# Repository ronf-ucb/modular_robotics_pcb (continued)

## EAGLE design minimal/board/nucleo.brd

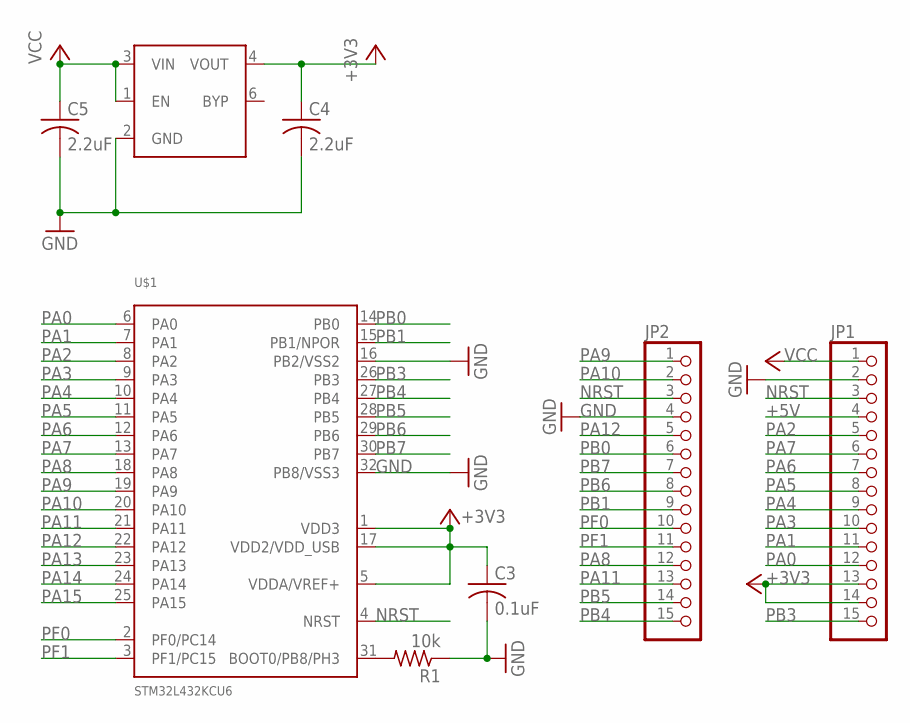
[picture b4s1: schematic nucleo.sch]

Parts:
C3: 0.1uF; C0402
C4, C5: 2.2uF; C0402
JP1, JP2: PINHD-1X15; 1X15
R1: 10k; R0402
U$1: STM32L432KCU6; QFN-32
U$3: MIC5305-MLF; MLF-6

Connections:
+3V3: C3.1, C4.1, JP1.13, JP1.14, U$1.1 (VDD3), U$1.5 (VDDA/VREF+), U$1.17 (VDD2/VDD_USB), U$3.4 (VOUT)
+5V: JP1.4
GND: C3.2, C4.2, C5.2, JP1.2, JP2.4, R1.1, U$1.16 (PB2/VSS2), U$1.32 (PB8/VSS3), U$3.2 (GND)
unnamed: R1.2, U$1.31 (BOOT0/PB8/PH3)
NRST: JP1.3, JP2.3, U$1.4 (NRST)
PA0: JP1.12, U$1.6 (PA0)
PA1: JP1.11, U$1.7 (PA1)
PA2: JP1.5, U$1.8 (PA2)
PA3: JP1.10, U$1.9 (PA3)
PA4: JP1.9, U$1.10 (PA4)
PA5: JP1.8, U$1.11 (PA5)
PA6: JP1.7, U$1.12 (PA6)
PA7: JP1.6, U$1.13 (PA7)
PA8: JP2.12, U$1.18 (PA8)
PA9: JP2.1, U$1.19 (PA9)
PA10: JP2.2, U$1.20 (PA10)
PA11: JP2.13, U$1.21 (PA11)
PA12: JP2.5, U$1.22 (PA12)
PA13: U$1.23 (PA13)
PA14: U$1.24 (PA14)
PA15: U$1.25 (PA15)
PB0: JP2.6, U$1.14 (PB0)
PB1: JP2.9, U$1.15 (PB1/NPOR)
PB3: JP1.15, U$1.26 (PB3)
PB4: JP2.15, U$1.27 (PB4)
PB5: JP2.14, U$1.28 (PB5)
PB6: JP2.8, U$1.29 (PB6)
PB7: JP2.7, U$1.30 (PB7)
PF0: JP2.10, U$1.2 (PF0/PC14)
PF1: JP2.11, U$1.3 (PF1/PC15)
VCC: C5.1, JP1.1, U$3.1 (EN), U$3.3 (VIN)

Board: 2 copper layers, 8 parts (0 on the bottom side), 27 nets, no tracks yet.

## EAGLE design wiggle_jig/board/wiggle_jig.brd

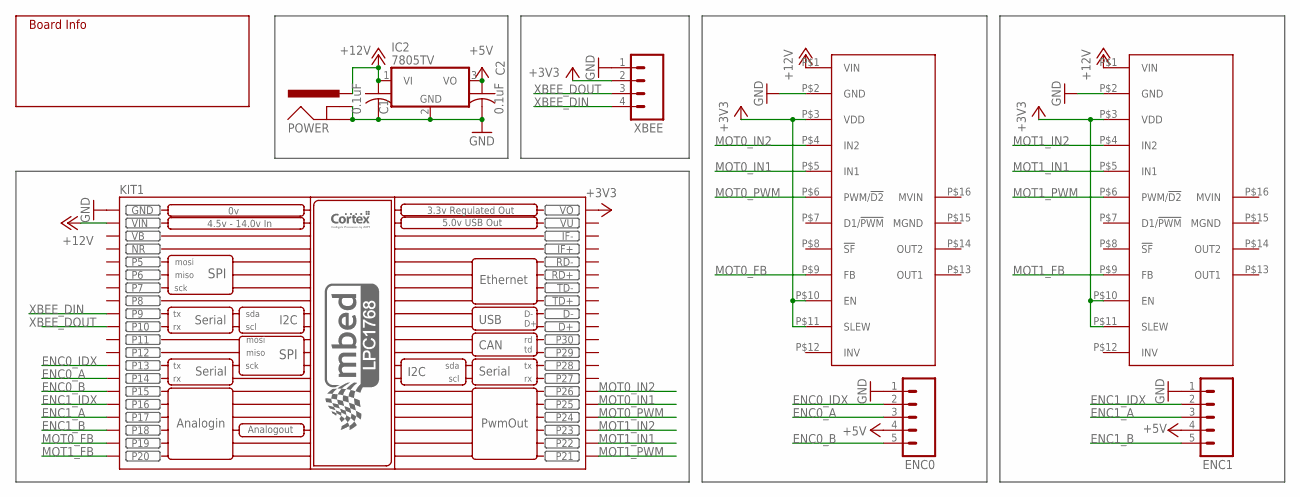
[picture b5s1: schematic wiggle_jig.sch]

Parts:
C1, C2: 0.1uF; C025-025X050
ENC0, ENC1: M05LOCK; 1X05_LOCK
IC2: 7805TV; TO220V
KIT1: MBED_NXP_LPC1768; MBED-KIT
MOT0, MOT1: MC33926_CARRIER
POWER: POWER_JACKPTH_LOCK; POWER_JACK_PTH_LOCK
U$4: INFO
XBEE: M04LOCK; 1X04_LOCK

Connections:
+3V3: KIT1.VOUT (VO), MOT0.P$3 (VDD), MOT0.P$10 (EN), MOT0.P$11 (SLEW), MOT1.P$3 (VDD), MOT1.P$10 (EN), MOT1.P$11 (SLEW), XBEE.2
+5V: C2.1, ENC0.4, ENC1.4, IC2.3 (VO)
+12V: C1.1, IC2.1 (VI), KIT1.VIN, MOT0.P$1 (VIN), MOT1.P$1 (VIN), POWER.PWR
ENC0_A: ENC0.3, KIT1.P$14 (P14)
ENC0_B: ENC0.5, KIT1.P$15 (P15)
ENC0_IDX: ENC0.2, KIT1.P$13 (P13)
ENC1_A: ENC1.3, KIT1.P$17 (P17)
ENC1_B: ENC1.5, KIT1.P$18 (P18)
ENC1_IDX: ENC1.2, KIT1.P$16 (P16)
GND: C1.2, C2.2, ENC0.1, ENC1.1, IC2.2 (GND), KIT1.GND, MOT0.P$2 (GND), MOT1.P$2 (GND), POWER.GND, POWER.GNDBREAK, XBEE.1
MOT0_FB: KIT1.P$19 (P19), MOT0.P$9 (FB)
MOT0_IN1: KIT1.P$25 (P25), MOT0.P$5 (IN1)
MOT0_IN2: KIT1.P$26 (P26), MOT0.P$4 (IN2)
MOT0_PWM: KIT1.P$24 (P24), MOT0.P$6 (PWM/!D2)
MOT1_FB: KIT1.P$20 (P20), MOT1.P$9 (FB)
MOT1_IN1: KIT1.P$22 (P22), MOT1.P$5 (IN1)
MOT1_IN2: KIT1.P$23 (P23), MOT1.P$4 (IN2)
MOT1_PWM: KIT1.P$21 (P21), MOT1.P$6 (PWM/!D2)
NR: KIT1.NR
VB: KIT1.VB
VU: KIT1.VU
XBEE_DIN: KIT1.P$9 (P9), XBEE.4
XBEE_DOUT: KIT1.P$10 (P10), XBEE.3

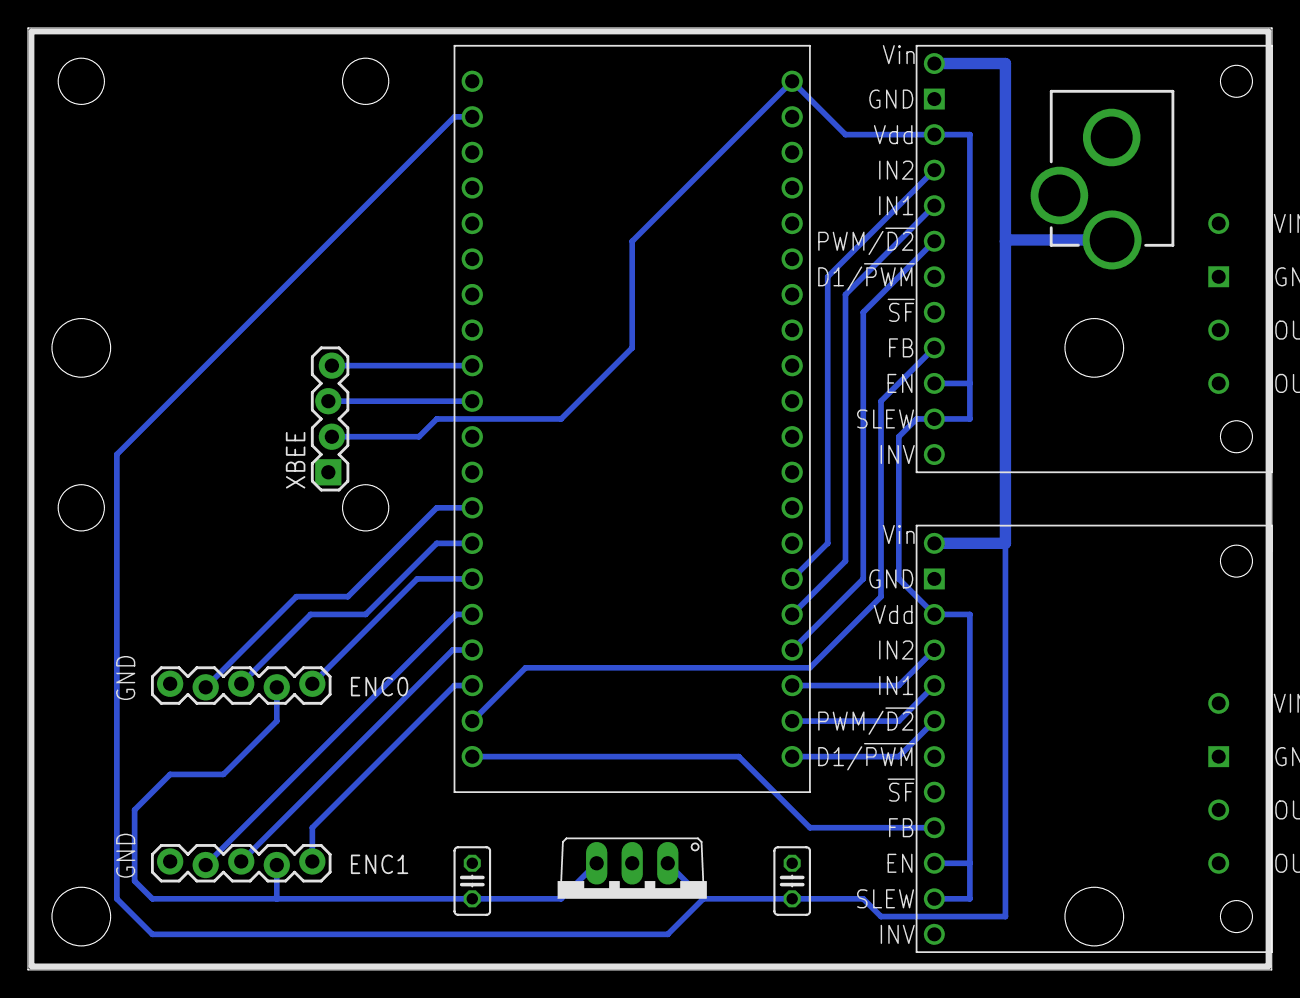
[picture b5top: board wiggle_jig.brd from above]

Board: 2 copper layers, 88.9 x 67.3 mm, 15 parts (0 on the bottom side), 20 nets.

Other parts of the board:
U$1, U$2, U$3, U$9: STAND-OFF

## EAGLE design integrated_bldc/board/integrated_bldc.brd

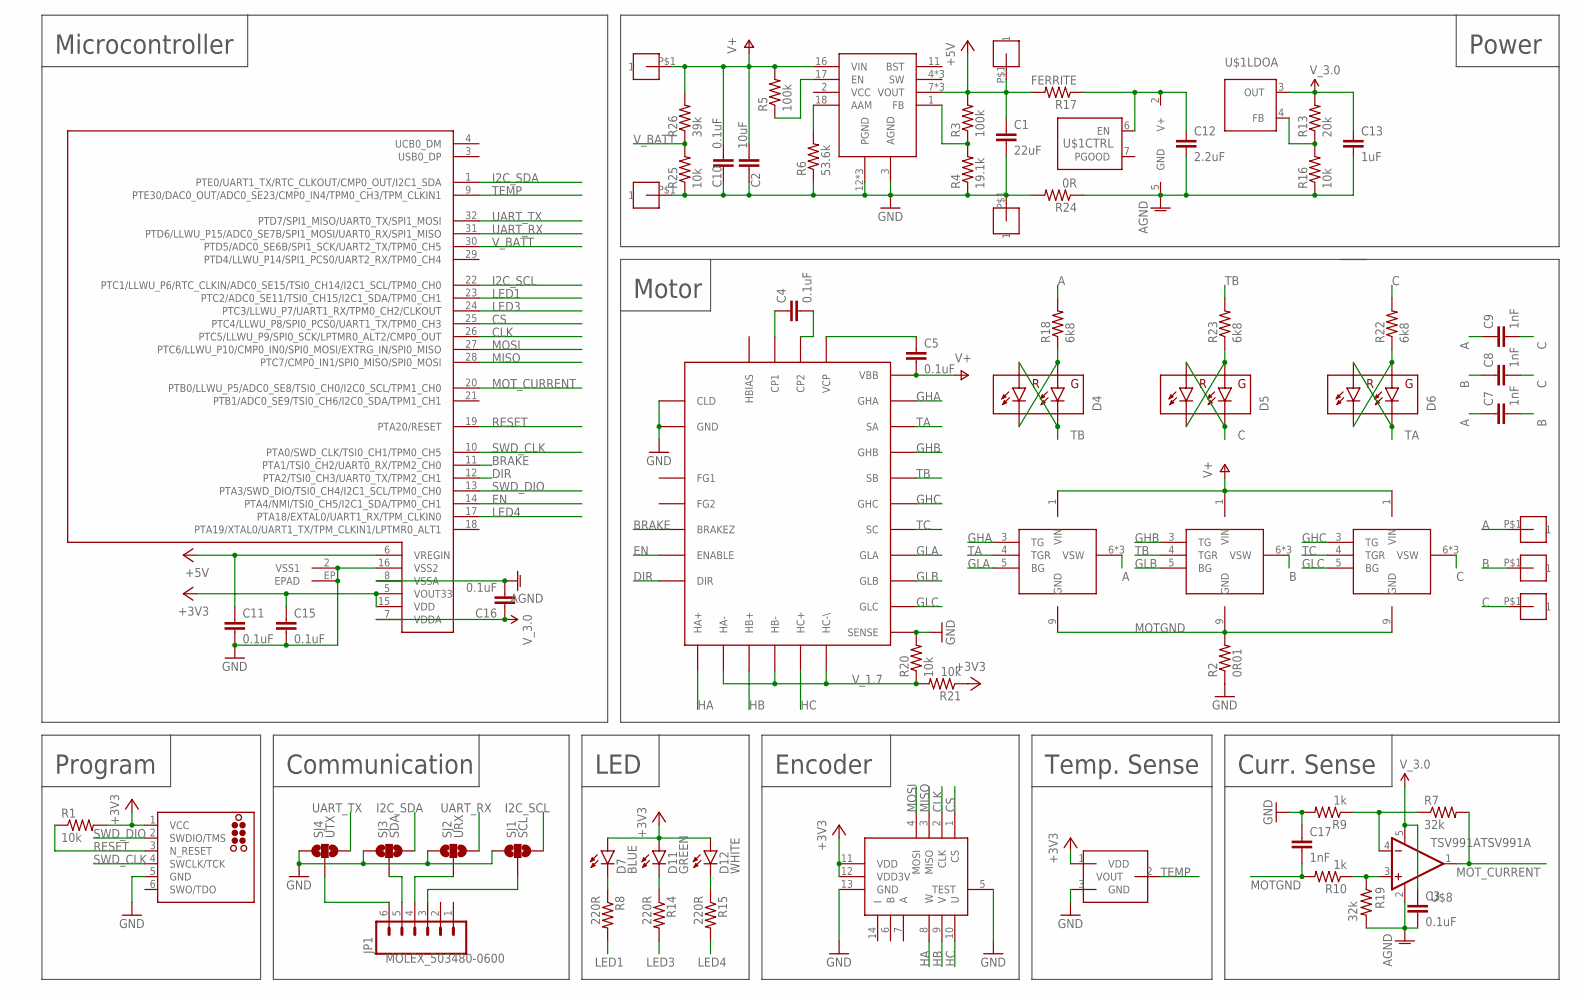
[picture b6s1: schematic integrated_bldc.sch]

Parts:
AS5047P: AS5047P; TSSOP14
C1: 22uF; 1210
C2: 10uF; 1206
C3, C4, C5, C11, C15, C16: 0.1uF; 0402-CAP
C7, C8, C9: 1nF; 0603-CAP
C10: 0.1uF; 0603-CAP
C12: 2.2uF; 0402-CAP; VOLTAGE 10V
C13: 1uF; 0402-CAP; VOLTAGE 6.3V
C17: 1nF; 0402-CAP
D4, D5, D6: LED-RGLTST-C195KGJRKT; LTST-C195KGJRKT
D7: BLUE; LED-0603
D11: GREEN; LED-0603
D12: WHITE; LED-0603
J2: PRG; TC2030-MCP-NL
JP1: MOLEX_503480-0600
R1, R16, R20, R21, R25: 10k; 0402-RES
R2: 0R01; 1206
R3, R5: 100k; 0402-RES
R4: 19.1k; 0402-RES
R6: 53.6k; 0402-RES
R7, R19: 32k; 0402-RES
R8, R14, R15: 220R; 0402-RES
R9, R10: 1k; 0402-RES
R13: 20k; 0402-RES
R17: FERRITE; R0603
R18, R22, R23: 6k8; 0402-RES
R24: 0R; 0402-RES
R26: 39k; 0402-RES
SJ1: SCL; SJ_TINY
SJ2: URX; SJ_TINY
SJ3: SDA; SJ_TINY
SJ4: UTX; SJ_TINY
U$1: SC560C; MLPQ-UT8
U$2: A4931SMT; 28-CONTACT-QFN-ET
U$3: MKL25Z128VFM4; QFN-32
U$4, U$5, U$6: MOSFET-HALFBRIDGECSD87333Q3D; SON8
U$7: MPM3610MPM3610GQV; QFN20
U$8: TSV991ATSV991A; SOT23-5
U$9: SOT_TEMP_SENSE; SOT23-3
U$10: A; SMD_MOT_PAD
U$11: B; SMD_MOT_PAD
U$12: C; SMD_MOT_PAD
VIN+: V+; SMD_BAT_PAD
VIN-: GND; SMD_BAT_PAD
VOUT+: A; SMD_MOT_PAD
VOUT-: A; SMD_MOT_PAD

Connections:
+3V3: AS5047P.11 (VDD), AS5047P.12 (VDD3V), C15.1, D7.A, D11.A, D12.A, J2.1 (VCC), R1.2, R21.1, U$3.5 (VOUT33), U$3.15 (VDD), U$9.1 (VDD)
+5V: C1.1, C11.1, R3.2, R17.2, U$3.6 (VREGIN), U$7.7 (VOUT), U$7.8 (VOUT), U$7.9 (VOUT), VOUT+.P$1
A: C7.1, C9.1, R18.2, U$5.6 (VSW), U$5.7 (VSW), U$5.8 (VSW), U$10.P$1
AGND: C3.2, C12.2, C13.2, C16.2, R16.1, R19.2, R24.1, U$1.5 (GND), U$3.8 (VSSA), U$8.2 (V-)
B: C7.2, C8.1, U$4.6 (VSW), U$4.7 (VSW), U$4.8 (VSW), U$11.P$1
BEN: R5.1, U$7.17 (EN)
BRAKE: U$2.28 (BRAKEZ), U$3.11 (PTA1/TSI0_CH2/UART0_RX/TPM2_CH0)
C: C8.2, C9.2, D5.P$2 (RA), D5.P$3 (GC), R22.2, U$6.6 (VSW), U$6.7 (VSW), U$6.8 (VSW), U$12.P$1
CLK: AS5047P.2 (CLK), U$3.26 (PTC5/LLWU_P9/SPI0_SCK/LPTMR0_ALT2/CMP0_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)
CS: AS5047P.1 (CS), U$3.25 (PTC4/LLWU_P8/SPI0_PCS0/UART1_TX/TPM0_CH3)
DIR: U$2.26 (DIR), U$3.12 (PTA2/TSI0_CH3/UART0_TX/TPM2_CH1)
EN: U$2.27 (ENABLE), U$3.14 (PTA4/NMI/TSI0_CH5/I2C1_SDA/TPM0_CH1)
FB: R3.1, R4.2, U$7.1 (FB)
GHA: U$2.21 (GHA), U$5.3 (TG)
GHB: U$2.19 (GHB), U$4.3 (TG)
GHC: U$2.17 (GHC), U$6.3 (TG)
GLA: U$2.16 (GLA), U$5.5 (BG)
GLB: U$2.15 (GLB), U$4.5 (BG)
GLC: U$2.14 (GLC), U$6.5 (BG)
GND: AS5047P.5 (TEST), AS5047P.13 (GND), C1.2, C2.2, C10.2, C11.2, C15.2, C17.1, J2.5 (GND), R2.1, R4.1, R6.1, R9.2, R20.2, R24.2, R25.1, SJ1.1, SJ2.1, SJ3.1, SJ4.1, U$2.7 (GND), U$2.13 (SENSE), U$2.25 (CLD), U$3.2 (VSS1), U$3.16 (VSS2), U$3.EP (EPAD), U$7.3 (AGND), U$7.12 (PGND), U$7.13 (PGND), U$7.14 (PGND), U$9.3 (GND), VIN-.P$1, VOUT-.P$1
HA: AS5047P.8 (W), U$2.1 (HA+)
HB: AS5047P.9 (V), U$2.3 (HB+)
HC: AS5047P.10 (U), U$2.5 (HC+)
I2C_SCL: SJ1.3, U$3.22 (PTC1/LLWU_P6/RTC_CLKIN/ADC0_SE15/TSI0_C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)
I2C_SDA: SJ3.3, U$3.1 (PTE0/UART1_TX/RTC_CLKOUT/CMP0_OUT/I2C1_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)
LED1: R8.2, U$3.23 (PTC2/ADC0_SE11/TSI0_CH15/I2C1_SDA/TPM0_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)
LED3: R14.2, U$3.24 (PTC3/LLWU_P7/UART1_RX/TPM0_CH2/CLKOUT)
LED4: R15.2, U$3.17 (PTA18/EXTAL0/UART1_RX/TPM_CLKIN0)
MISO: AS5047P.3 (MISO), U$3.28 (PTC7/CMP0_IN1/SPI0_MISO/SPI0_MOSI)
MOSI: AS5047P.4 (MOSI), U$3.27 (PTC6/LLWU_P10/CMP0_IN0/SPI0_MOSI/EXTRG_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)
MOTGND: C17.2, R2.2, R10.2, U$4.9 (GND), U$5.9 (GND), U$6.9 (GND)
MOT_CURRENT: R7.2, U$3.20 (PTB0/LLWU_P5/ADC0_SE8/TSI0_CH0/I2C0_SCL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), U$8.1 (OUT)
unnamed: R7.1, R9.1, U$8.4 (-IN)
unnamed: R10.1, R19.1, U$8.3 (+IN)
unnamed: D4.P$1 (GA), D4.P$4 (RC), R18.1
unnamed: D7.C, R8.1
unnamed: R6.2, U$7.18 (AAM)
unnamed: D11.C, R14.1
unnamed: D12.C, R15.1
unnamed: R13.1, R16.2, U$1.4 (FB)
unnamed: D5.P$1 (GA), D5.P$4 (RC), R23.1
unnamed: C12.1, R17.1, U$1.2 (V+), U$1.6 (EN)
unnamed: D6.P$1 (GA), D6.P$4 (RC), R22.1
unnamed: C5.1, U$2.12 (VCP)
unnamed: C4.1, U$2.9 (CP1)
unnamed: C4.2, U$2.10 (CP2)
unnamed: JP1.6, SJ4.2
unnamed: JP1.5, SJ3.2
unnamed: JP1.4, SJ2.2
unnamed: JP1.3, SJ1.2
RESET: J2.3 (N_RESET), R1.1, U$3.19 (PTA20/RESET)
SWD_CLK: J2.4 (SWCLK/TCK), U$3.10 (PTA0/SWD_CLK/TSI0_CH1/TPM0_CH5)
SWD_DIO: J2.2 (SWDIO/TMS), U$3.13 (PTA3/SWD_DIO/TSI0_CH4/I2C1_SCL/TPM0_CH0)
TA: D6.P$2 (RA), D6.P$3 (GC), U$2.22 (SA), U$5.4 (TGR)
TB: D4.P$2 (RA), D4.P$3 (GC), R23.2, U$2.20 (SB), U$4.4 (TGR)
TC: U$2.18 (SC), U$6.4 (TGR)
TEMP: U$3.9 (PTE30/DAC0_OUT/ADC0_SE23/CMP0_IN4/TPM0_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), U$9.2 (VOUT)
UART_RX: SJ2.3, U$3.31 (PTD6/LLWU_P15/ADC0_SE7B/SPI1_MOSI/UART0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)
UART_TX: SJ4.3, U$3.32 (PTD7/SPI1_MISO/UART0_TX/SPI1_MOSI)
V+: C2.1, C5.2, C10.1, R5.2, R26.2, U$2.11 (VBB), U$4.1 (VIN), U$5.1 (VIN), U$6.1 (VIN), U$7.16 (VIN), VIN+.P$1
V_1.7: R20.1, R21.2, U$2.2 (HA-), U$2.4 (HB-), U$2.6 (HC-\)
V_3.0: C3.1, C13.1, C16.1, R13.2, U$1.3 (OUT), U$3.7 (VDDA), U$8.5 (V+)
V_BATT: R25.2, R26.1, U$3.30 (PTD5/ADC0_SE6B/SPI1_SCK/UART2_TX/TPM0_C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)

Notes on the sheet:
Motor
Power
Curr. Sense
Temp. Sense
Encoder
LED
Communication
Program
Microcontroller

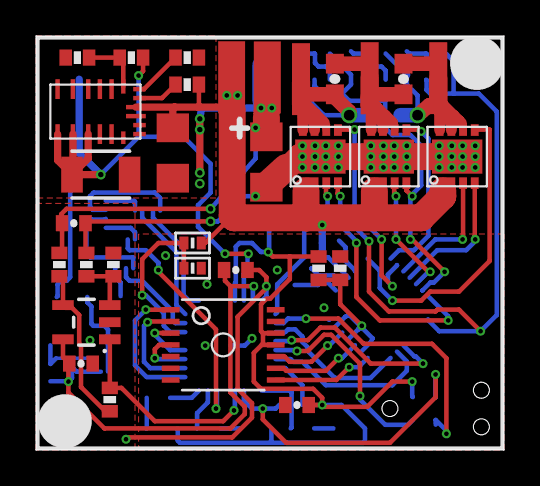
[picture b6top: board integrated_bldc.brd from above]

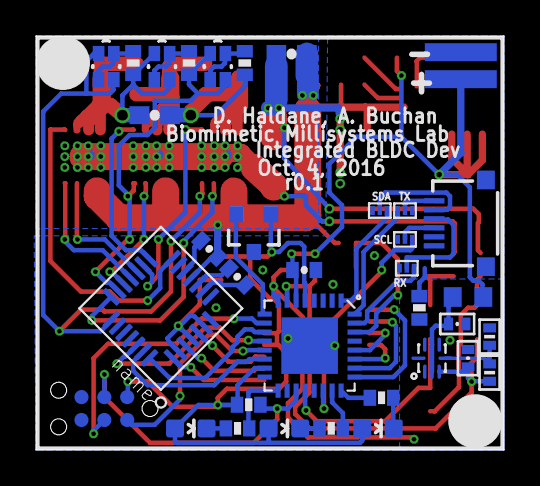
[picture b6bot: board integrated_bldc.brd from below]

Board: 2 copper layers, 26.0 x 23.0 mm, 69 parts (37 on the bottom side), 63 nets.

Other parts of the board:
U$16: INFO

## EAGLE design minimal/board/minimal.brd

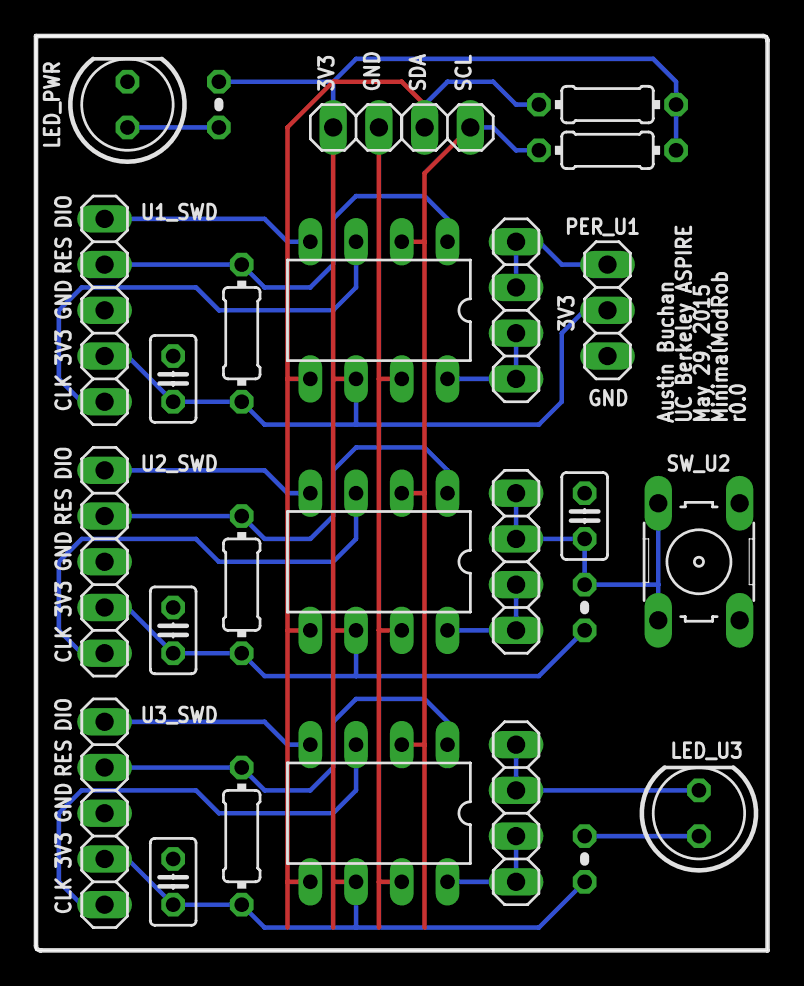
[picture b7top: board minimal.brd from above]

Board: 2 copper layers, 40.6 x 50.8 mm, 28 parts (0 on the bottom side), 21 nets.

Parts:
C1, C2, C3, C4: 100nF; C025-025X050
I2C: 1X02
LED_PWR: LED5MM
LED_U3: LED5MM
PER_U1: 1X03
PWR: 1X02
R1, R2: 4k7; 0204/7
R3: 10k; 0204V
R4, R5: 1k; 0204V
R6, R7, R8: 10k; 0204/7
SW_U2: B3F-10XX
U1, U2, U3: LPC810M021FN8FP-DIL08; DIL08
U1_IO, U2_IO, U3_IO: 1X04
U1_SWD, U2_SWD, U3_SWD: 1X05
U$1: INFO

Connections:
+3V3: C1.1, C2.1, C3.1, PER_U1.2, PWR.1, R1.2, R2.2, R3.2, R4.2, R5.2, R6.2, R7.2, R8.2, U1.6, U1_SWD.4, U2.6, U2_SWD.4, U3.6, U3_SWD.4
GND: C1.2, C2.2, C3.2, C4.2, LED_PWR.K, PER_U1.1, PWR.2, SW_U2.1, SW_U2.2, U1.7, U1_SWD.3, U2.7, U2_SWD.3, U3.7, U3_SWD.3
I2C_SCL: I2C.1, R1.1, U1.2, U2.2, U3.2
I2C_SDA: I2C.2, R2.1, U1.5, U2.5, U3.5
unnamed: LED_PWR.A, R5.1
unnamed: C4.1, R3.1, SW_U2.3, SW_U2.4, U2_IO.3, U2_IO.4
unnamed: PER_U1.3, U1_IO.3, U1_IO.4
unnamed: LED_U3.A, R4.1
unnamed: LED_U3.K, U3_IO.3, U3_IO.4
U1_IO: U1.8, U1_IO.1, U1_IO.2
U1_RESET: R6.1, U1.1, U1_SWD.2
U1_SWCLK: U1.3, U1_SWD.5
U1_SWDIO: U1.4, U1_SWD.1
U2_IO: U2.8, U2_IO.1, U2_IO.2
U2_RESET: R7.1, U2.1, U2_SWD.2
U2_SWCLK: U2.3, U2_SWD.5
U2_SWDIO: U2.4, U2_SWD.1
U3_IO: U3.8, U3_IO.1, U3_IO.2
U3_RESET: R8.1, U3.1, U3_SWD.2
U3_SWCLK: U3.3, U3_SWD.5
U3_SWDIO: U3.4, U3_SWD.1

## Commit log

2014-02-10 Initial commit with rough layout of board
2014-02-11 Switched I2C and Charge pins for better Arduino compatability. Adding dev version
2014-02-11 Added parallel pull-up to status
2014-02-11 Working on layout
2014-02-11 Layout complete. Need to fix some crossing wires, tidy up, figure out if need to fix A4/A2 connection issue.
2014-02-12 Finished layout, round 2
2014-02-13 Prepared silkscreen
2014-02-13 Added encoder boards
2014-02-14 Should have all parts in for camera adapter board
2014-02-14 Schematic more or less done, moving to layout
2014-02-15 Pmod signal routing more or less done
2014-02-17 Most layout done
2014-02-17 Layout done
2014-02-19 Fixing small things preparing for panelization
2014-02-19 Working on panelizing makefile
2014-02-19 board.zip targets work
2014-02-19 All boards target works
2014-02-20 Updated CAM file and script to match, include names and values in solder mask
2014-02-20 Merging to panel works with makefile now
2014-02-21 Got rid of holes in 20 csp through package. Preparing for job submission pending spacing check.
2014-02-21 Fixed annular ring problem and made motor vias bigger
2014-02-22 Board and component orders placed
2014-03-06 Fixed 10k label
2014-07-16 Moved pullup on charge management status to vbus
2014-07-19 Working on motor layout for modular motor driver
2014-07-19 Motor driver laid out
2014-07-22 Working on final traces
2014-07-24 Rough routing done, need to polish
2014-07-24 Full routing done. Need to do silkscreen
2014-09-09 Commiting before branching on OVM7660 camera board, not sure what the updates to motor_module are
2014-09-09 Added note about camera voltages
2014-09-11 Updated to r0.1. Fixed reset problems. Should be ready for shipping
2014-09-12 Fixed spacing for TCM camera pads, updated pullup resitor val on reset line
2014-09-12 Laying out smaller TCM camera board
2014-09-12 Finished routing, silkscreen done, ready for panelization
2014-09-13 Updated BOM with all parts for camera. Updated camera to have larger isolate to avoid overzealous autodfm errors
2014-09-13 Adding layout files for 2014_09_12 order
2014-09-15 Updating Make structure to use cam.sh in each board directory for CAM
2014-09-15 Panelization with Zumy boards
2014-09-26 Import of BLDC from before the existance of modular_robotics_pcb. This import will probably bork the history.
    Current state of board: Schematic DONE, 274 airwires left in PCB
2014-09-26 Routed power management (Reverse Polarity, battery sense, vreg) section.
    245 airwires.
2014-09-26 Added 3 planes for SH_A,SH_B, SH_C. Modifired DRV thermal footprint to be consistant with datasheet. Routed a lot of the DRV-components through the gap added by the right footprint.
    Down to 163 airwires.
2014-09-27 97 airwires.
    Most of the powermosfets are routed.
    Most of the encoder is routed
2014-09-27 11 airwires left.
    Made major routes everywhere. Need to think, clear head, and clean up some of the connections.
    Some connections are getting 3+ vias, which can be improved w/ thought.
2014-09-29 First route with zero airwires. Still haven't run DRC.
2014-09-29 Fixed DRC to have 6mil clearance, fixed DRC errors.
2014-09-30 Added bigger GND planes, motor mount holes
2014-09-30 should have deleted pdf files
2014-09-30 should have deleted pdf files..
2014-10-01 Working on KL05Z debugging
2014-10-01 Fixed simlink
2014-10-03 Added bldc panelization, and starting to make sensor ADC board
2014-10-03 Schematic pretty much done, need to pinswap before layout
2014-10-04 Rough layout getting there
2014-10-05 ADC layout mostly done, just need to finish bonus parts
2014-10-06 Layout pretty much done, need to clean up schematic and do silkscreen
2014-10-06 Tweak capacitor, made BLDC + ADC panel.
2014-10-06 Fixed arduino name
2014-10-07 Fixed encoder alignment. May still need to fix holes for BLDC motor
2014-10-07 Corrected BLDC mounting holes, added borders to boards, squeezed one more ADC board in to panelization
2014-10-07 Updated BOM for ZedBoard/ADC adapter
2015-01-17 Last changes before 2014_11_18 order
2015-05-28 Adding minimal test design schematic
2015-11-10 Footprints for gearmotor header and motor driver carrier
2015-11-10 Add symbols and devices
2015-12-01 Adding all boards for minimal and carrier board with MKL05Z32
2016-03-03 Adding TQFP package
2016-09-23 Initial commit of integrated bldc board.
2016-09-26 Updated integrated BLDC controller schematic to include isolated analog ground, differential current sense amp. and battery voltage sense.
2016-09-26 Adding changes to modular robotics library.
2016-09-26 Added tiny solderjumper to modular robotics library.
2016-09-26 Working on layout.
2016-09-27 First pass at layout done.
2016-09-28 Integrated BLDC is clean from Bay Area Circuits DFM check.
2016-10-04 Working on dev version of integrated bldc. Still need to route digital power.
2016-10-04 Finished Dev board layout. Added stop mask to vias. Corrected some component values based on part order.
2016-10-05 Added dev integrated BLDC to panel.
2016-10-05 Fixed spacing on DC-DC converter, updated all polygons to 0.15mm isolate for good measure.
2016-10-05 Fixed one more polygon spacing.
2016-10-11 Starting on micro mirror board.
2016-10-12 Layout pretty much done, need to do silkscreen.
2016-10-12 Added section labelling on schematic.
2016-10-13 Submitted micro mirror for DFM
2016-10-13 Expanded board to enclose high voltage areas, added a few more labels
2016-10-13 Tiled micro mirror board. Added author info etc. Used extra buffers in full channels for additional drive isolation. Added border.
2016-10-19 Added wiggle jig.:
2017-01-05 Added minimal nucleo design.
2017-03-17 Create LICENSE
2018-06-08 updates from Austin through Aug 2017
2018-06-08 start adding code for K64F to drive high voltage board
2018-06-08 aded FreeRTOS to repo
2018-06-08 added launch file as well
2018-06-08 added DAC output pin
2018-06-08 added .mex file and DAC out
2018-06-08 started to add DAC code
2018-06-09 DAC ramp working, A/D interrupt not triggering
2018-06-09 added polling A/D. still issues with printing to queue from inside interrupt...
2018-06-15 fixes to component values (decrease current)
2018-06-20 in progress, changing copper spacing
2018-07-03 bigger gap for output connectors
2018-07-06 making gap > 40 mil to handle 1kV.
2018-07-11 changed to ribbon cable connectors with K64F pinouts for ease of connect. Need to change lm324 to rail-to-rail
2018-07-12 added mounting holes, and some extra libraries in common
2018-07-19 started digikey BOM. consolidated resistor values for ease of assembly.
2018-07-20 added caps to BoM
2018-07-20 added rest of parts
2018-07-21 added k64F connection .pdf
2018-08-13 rev 1.1. starting to fix some design errors, cearance issues in version 1.0 near diodes. version 4. Keep version 3 for documentation purposes for 1.0.
2018-08-14 cleaning up schematic warnings
2018-08-14 still need to do correct merge of vdd and vdda
2018-08-15 added voltage divider for HV out in case needed
2018-09-06 initial commit of Loren's 4 channel drive code
2019-06-21 draft switching to charge pummp
2019-06-22 adding 2x2 array
2019-06-27 updated library to include 1:10 xfmr
2019-06-28 placing flash boost converter
2019-07-01 started routing of wing actuator drive
2019-07-02 more routing and adding ground plane
2019-07-02 done routing. need to add attributes for BoM
2019-07-03 renumbered parts
2019-07-04 added digikey part #s
2019-07-08 changed all lines to 8 mil min width
2019-07-08 added Eagle notes to repo
2019-07-10 updated library, and added prefix
2019-07-10 initial commit for tactile project, using ee192 racetimer as starting point
2019-07-10 b.o.m. for actuator drive board
2019-07-12 added show_help for sensor program
2019-07-12 added J6 pins for scanclk etc in pin_mux.c
2019-07-12 updated notes- need to CR_INTEGER_PRINTF - Undefine/Remove this directive and set PRINTF_FLOAT_ENABLE=1 in settings
2019-07-13 added atod module- need to get GETCHAR working to select menu item (and later for python communication)
2019-07-25 added help menu
2019-07-25 added tactdisp
2019-07-25 updated labels on PCB
2019-07-25 added simple read_frame
2019-07-26 moved interrupt for sync out to port D.
2019-07-26 merged notes
2020-07-13 adding Flash Trigger, generating HV from flash driver
2020-07-14 start of high voltage control project, with working UART
